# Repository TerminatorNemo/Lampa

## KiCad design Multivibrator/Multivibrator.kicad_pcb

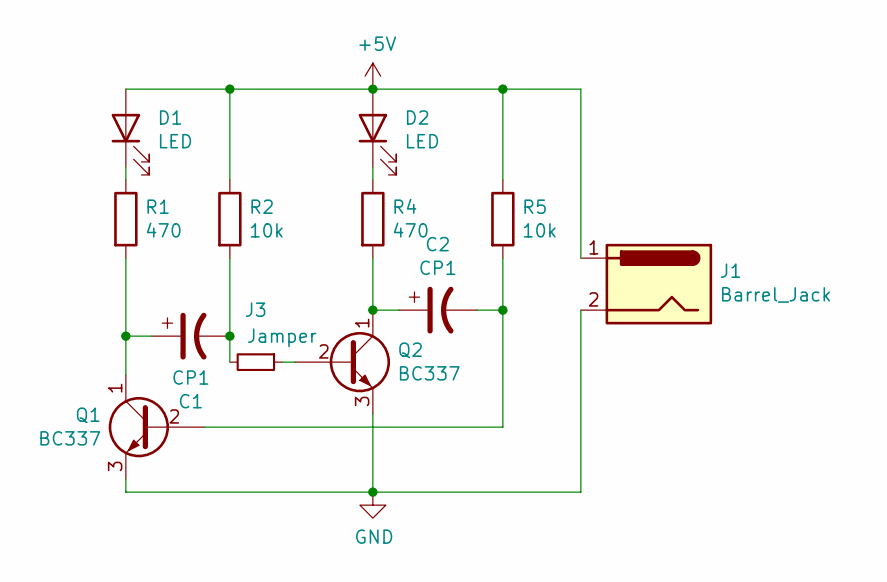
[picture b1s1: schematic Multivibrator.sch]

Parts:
C1, C2: CP1; CP_Elec_5x5.7
D1, D2: LED; D_0201_0603Metric
J1: Barrel_Jack; BarrelJack_Horizontal
J3: Jamper; R_Axial_DIN0207_L6.3mm_D2.5mm_P2.54mm_Vertical
Q1, Q2: BC337; TSOT-23
R1, R4: 470; R_0805_2012Metric
R2, R5: 10k; R_0805_2012Metric

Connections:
+5V: D1.2 (A), D2.2 (A), J1.1, R2.1, R5.1
GND: J1.2, Q1.3 (E), Q2.3 (E)
unnamed: C1.1, Q1.1 (C), R1.2
unnamed: C1.2, J3.2, R2.2
unnamed: C2.1, Q2.1 (C), R4.2
unnamed: C2.2, Q1.2 (B), R5.2
unnamed: D1.1 (K), R1.1
unnamed: D2.1 (K), R4.1
unnamed: J3.1, Q2.2 (B)

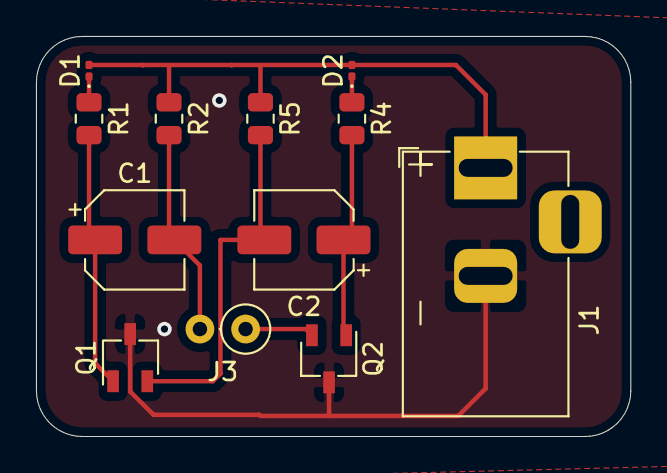
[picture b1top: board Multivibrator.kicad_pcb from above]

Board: 2 copper layers, 33.0 x 22.2 mm, 12 parts (0 on the bottom side), 9 nets.
